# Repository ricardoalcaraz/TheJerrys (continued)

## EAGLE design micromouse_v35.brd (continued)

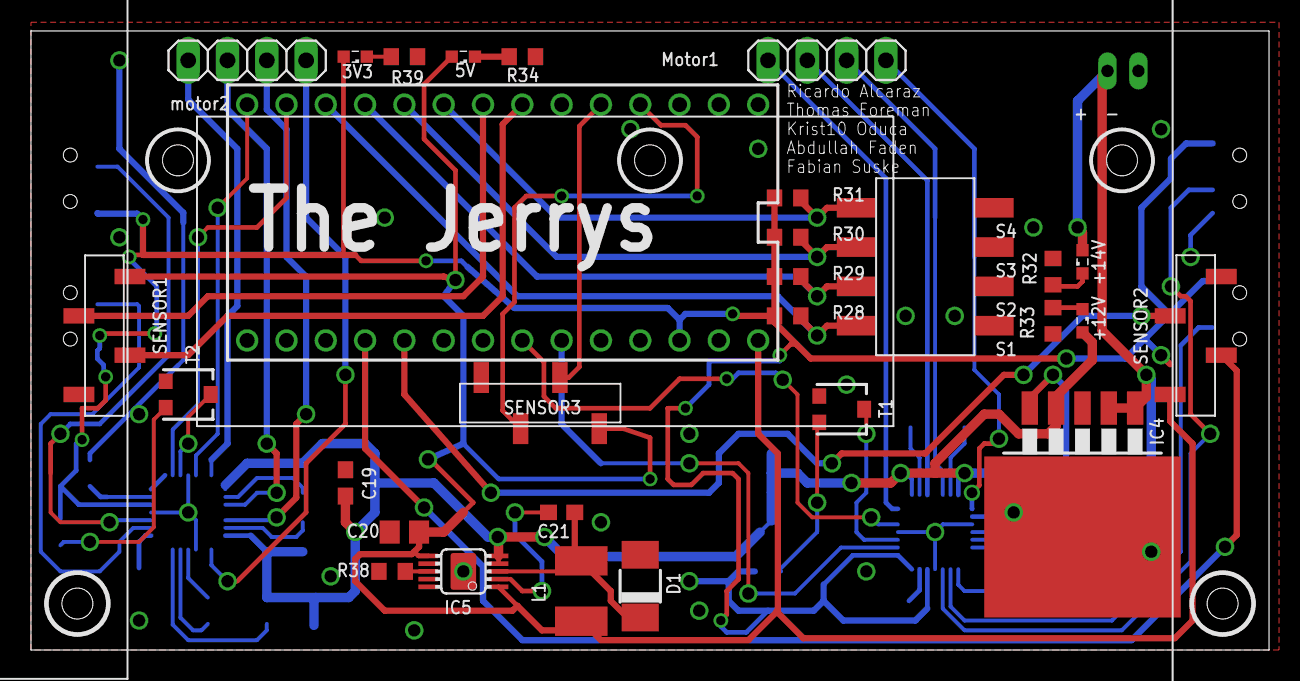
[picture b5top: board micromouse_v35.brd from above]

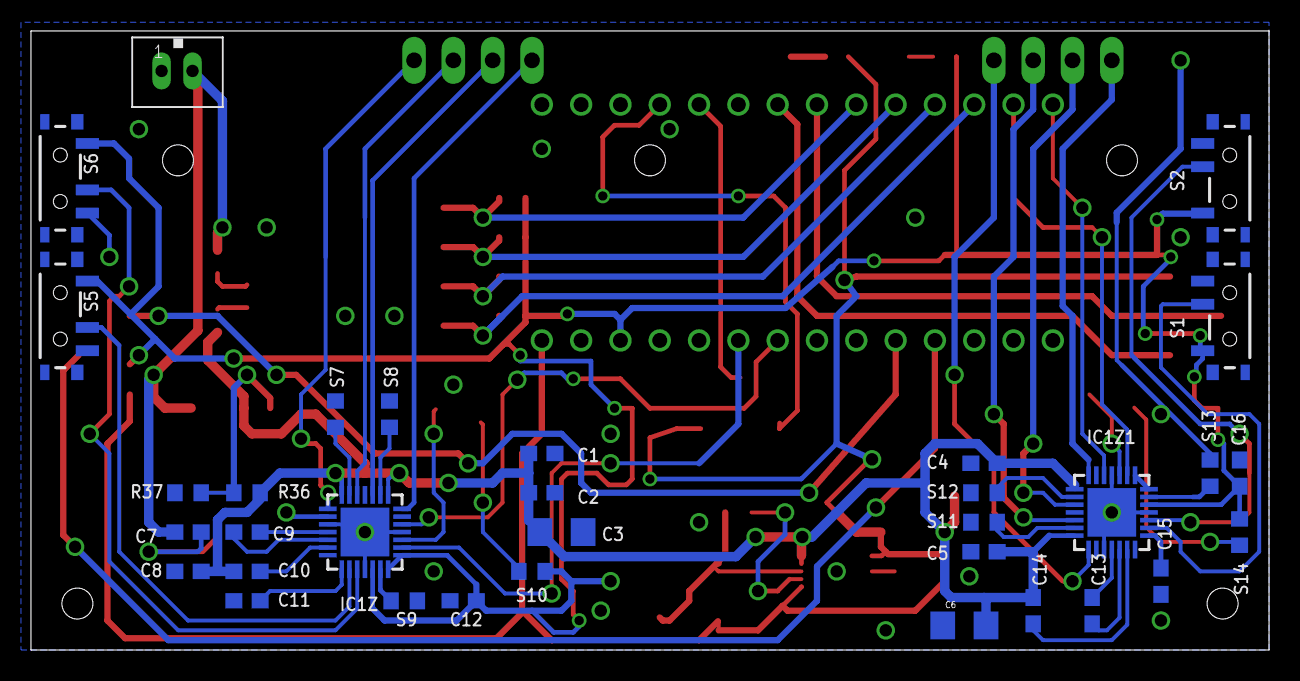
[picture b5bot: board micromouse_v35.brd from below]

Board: 2 copper layers, 80.0 x 40.0 mm, 62 parts (33 on the bottom side), 57 nets.

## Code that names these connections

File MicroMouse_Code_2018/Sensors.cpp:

#include "Sensors.h"

//Initializing an external functions so ISR can run properly
static void sensorISR();

//Pinout for the ultrasonic sensors
const uint8_t ECHO1 = 8;
const uint8_t ECHO2 = 2;
const uint8_t ECHO3 = 10;
const uint8_t TRIG1 = 9;
const uint8_t TRIG2 = 3;
const uint8_t TRIG3 = 11;
volatile double Sensors::runningAvgLeft[arraySize]={};
volatile double Sensors::runningAvgRight[arraySize]={};
volatile double Sensors::runningAvgMiddle[arraySize]={};

//Constructor
Sensors::Sensors( ) {
	//Set all the running average arrays to zero
	for( int i = 0; i < arraySize; i++ ) {
		runningAvgLeft[i] = 0;
		runningAvgRight[i] = 0;
		runningAvgMiddle[i] = 0;
	}
	timeout = 6000;
	interval = 10000;
}

//Initialize the pins for all the sensors
//Currently setup for ultrasonic sensors
void Sensors::init( uint32_t interval ) {
  	pinMode( ECHO2 ,INPUT );
  	pinMode( ECHO1 ,INPUT );
  	pinMode( ECHO3 ,INPUT );
  	pinMode( TRIG1 ,OUTPUT );
  	pinMode( TRIG2 ,OUTPUT );
  	pinMode( TRIG3 ,OUTPUT );
	this->interval = interval;
	sensorTimer.begin( sensorISR, this->interval );
	sensorTimer.priority( 50 );
}

void Sensors::setTimeout( uint32_t timeout ) {
	this->timeout = timeout;
}

//Return the averaged out right distance
double Sensors::getRightDistance( ) {
	uint16_t sum = 0;
	for( int i = 0; i < arraySize; i++ ) {
		sum += runningAvgRight[i];
	}
	double avg = sum/(double)arraySize+1;
	return avg;
}

//Return the averaged out left distance
double Sensors::getLeftDistance( ) {
	noInterrupts();
	double sum = 0;
	for( int i = 0; i < arraySize; i++ ) {
		sum += runningAvgLeft[i];
	}
	double avg = sum/(double)arraySize+1;
	interrupts();
	return avg;
}

//Return the averaged out middle distance
double Sensors::getMiddleDistance( ) {
	noInterrupts();
	double sum = 0;
	for( int i = 0; i < arraySize; i++ ) {
		sum += runningAvgMiddle[i];
	}
	interrupts();
	return sum/(double)arraySize+1;
}

//Update all the distances of the sensors
//and input them into the running average array
void Sensors::updateDistances() {
	static volatile uint8_t index = 0;
	static volatile uint8_t sensorCount = 0;
	switch( sensorCount ) {
		case 0:
			runningAvgLeft[index] = pingLeft();
			break;
		case 1:
			runningAvgRight[index] = pingRight();
			break;
		case 2:
			runningAvgMiddle[index] = pingMiddle();
			break;
	}
	index++;
	sensorCount++;
	if( index == arraySize ) index = 0;
	if( sensorCount == 3 ) sensorCount = 0;
}

//Return a single instance of the right sensor
volatile double Sensors::pingRight() {
      digitalWrite(TRIG2, LOW);
    delayMicroseconds(2);
    digitalWrite(TRIG2, HIGH);
    delayMicroseconds(10);
    digitalWrite(TRIG2, LOW);

    //Read the echo pin
    int duration = pulseIn(ECHO2, HIGH, timeout);

    //Calculate distance
    double distance = (double) duration*0.034/2;

    return distance;
}

//Return a single instance of the middle sensor
volatile double Sensors::pingLeft() {
    digitalWrite(TRIG3, LOW);
  	delayMicroseconds(2);
  	digitalWrite(TRIG3, HIGH);
  	delayMicroseconds(10);
  	digitalWrite(TRIG3, LOW);

  	//Read the echo pin
  	int duration = pulseIn(ECHO3, HIGH, timeout);

  	//Calculate distance
  	double distance = (double) duration*0.034/2;

  	return distance;
}

//Return a single instance of the middle sensor
volatile double Sensors::pingMiddle() {
  	digitalWrite(TRIG1, LOW);
  	delayMicroseconds(2);
  	digitalWrite(TRIG1, HIGH);
  	delayMicroseconds(10);
  	digitalWrite(TRIG1, LOW);

  	//Read the echo pin
  	int duration = pulseIn(ECHO1, HIGH, timeout);

  	//Calculate distance
  	double distance = (double) duration*0.034/2;

  	return distance;
}

Sensors sensorInterrupt;

//External interrupt function that points toward internal function, it's somewhat hacky but it works.
static void sensorISR() {
	sensorInterrupt.updateDistances();
}

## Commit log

2017-06-12 Added new schematic and board
2017-06-12 added motor control wiring
2017-06-12 Added sensor pins
2017-06-12 Added git ignore file
2017-06-12 Added small description of our project
2017-06-12 Added sensor pins to schematic
2017-06-12 Fixed Readme
2017-06-12 Finished Schematic Draft
2017-06-12 Fixed some inconsistencies
2017-07-20 Finalized Design
2017-07-20 Final final design
2017-07-20 Added 4pm to .gitignore
2017-07-20 Added description to readme
2017-07-20 Added ultrasonic sensor functions
2017-07-20 Added stepper motor + H bridge comm file that draws 0 current when inactive
2017-07-21 Fixed ability to read distances in serial monitor
    Added Serial.begin(9600) in order to initiate ability to read. Prior to this, sensor worked, but user could not read an output to confirm sensor's working ability. Additionally shifted delay after ch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
2017-07-21 Changed pulseMiddle() function to be able to output a distance
    pulseMiddle() used to just record and print distance. After changing its void return type to an int, it can now be treated as a variable and spit out a distance in cm. This will make it easier to eng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
2017-07-21 Replicated changes from pulseMiddle() to pulseRight() and pulseLeft()
    Lets user know when mouse can turn to make it easier to exxecute a turn. NOTE: if a single sensor gets very blocked as it nears an opening, measurements become really off and reach 3000cm. Since the 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
2017-07-21 Added file that combines sensor and motor
    Lets motor turn when sensor senses a gap. Still expends no current.
2017-07-21 Limit distance on sensors
    By setting the maximum time the sensor waits for a pulse, we can limit the maximum distance the pulse records. In this case, the sensor has been limited to 80cm.
2017-07-21 Updated combined sensor and motors to implement sensor range limitation
2017-07-22 Wrote code to implement a second motor
    Duplicated code and reassigned variable names. Cars will rotate on axis instead of pivoting. Therefore motor turning functions have both motors work at same time instead of having independent turning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
2017-07-22 Added turning functions given different pulses
2017-07-22 Added actual pin assignment for motors to the prototype board pin assignment
    Just comment out the prototype board/actual as necessary.
2017-07-25 Added file to start writing algorithm
    Will be able to solve using left hand rule and optimize for shortcuts
2017-07-25 renamed to more convenient variables
    Changed pins as well. in1Motor1 is now LMotor1
2017-07-25 Added switch functionality
    Using four switches in a case select scenario, we can 16 different possible outputs.
2017-07-25 Added new stepper library and functions
2017-07-26 consolidated useful functions in main file
2017-07-26 added missing code
2017-07-26 Wrote majority of algorithm pseudo-code
2017-07-26 Wrote additional code
    Got most of the logic for solving the maze and decision process written. Have not been able to test. Left FIXME comments for more experienced programmers to have a look at.
2017-07-26 Added comments describing various functions and fixed some setup code
2017-07-27 Edited code variables and included convenience delay
    Renamed motor pins to be motorLeft and motorRight instead of motor1 and motor 2. Additionally, there will be a delay after we flick the switch before the mouse starts working.
2017-07-27 Changed moveLeft and moveRight functions
    moveleft and move right no longer spin on its axis. It now pivots with one wheel stationary and the other incrementing steps. The functions are now named turnLeft() and turnRight(). Also removed the 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
2017-07-27 Combined all algorithm code into main micromouse.ino file.
2017-07-27 Ricardo, Khan, and Rosswell wrote code at same time via google docs
2017-07-27 Added a file to start simulating a maze and decision making
2017-07-27 Wrote a testbench for algorithm turning
    Program shows that it can optimize the path
2017-07-28 Ricardo and I group coded
    Wrote code to add letters and recall them to the directions as well as optimize.
2017-07-28 Fixed some compilation errors
2017-07-28 Fixed movment bugs
    corrected amount of steps bot shouyld take before it stop and decides again
2017-07-29 Consolidated bot functions into a new library
2017-07-29 Cleaned up some comments
2017-07-29 Begun adding ultrasonic sensor functions
    Only added basic pin assignments and setup
2017-07-29 added debug print statements
2017-07-29 Removed duplitcate
2017-07-29 Fixed pathing logic and started fine tuning movements
2017-07-29 Updated step counts
    steps cannot be 1 or else it will not move
2017-07-29 Changed middleDistance threshold to increase clearance when turning around
2017-07-29 Added path correcting to library
2017-07-29 Added path correction and minor micromouse.ino files
2017-07-29 Deleted jerry and stepper libraries as they should be in same folder level as main micromouse.ino
2017-07-29 No idea
2017-07-29 Revert "Deleted jerry and stepper libraries as they should be in same folder level as main micromouse.ino"
    This reverts commit 5623b765bdf1a9f3894e21da4fe20d62e673050c.
2017-08-01 Added last seconds corrections
2017-08-16 Added distance averaging
    Now has a small buffer and records 3 distances. The distance that is given is the median of 3 recordings to reduce the chance of an erroneous reading
2017-08-24 Fixed various compilation errors
2017-08-25 Fixed compilation errors
2017-08-25 Made comments to lgoic
2017-08-27 Added some commentary to the logic behind maze solving
2017-09-05 Added descriptions to various functions
2017-11-02 Testbenched method to check if mouse found goal
2017-11-02 Wrote code to test if mouse found goal
    Wrote isGoal() to check if three right turns were made in a row while under a set number of steps. Since I learned about pointers, I wrote clearCounter() to clear the steps made unless a right turn w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
2017-11-18 Changed algorithm tests to use address passing
2018-01-25 Polished board and added names
2018-03-11 Added makeTurn() function
2018-03-11 Added another simulation based on an actual maze
2018-03-11 Deleted unnecessary files
2018-03-11 Cleaned up some files
2018-03-11 Transfered test algorithm code to micromouse.ino
2018-03-12 Added file to test intersections
2018-03-12 Started 2018 board revision for micromouse
2018-03-12 Added power switch to schematic
2018-03-20 Added power circuit
2018-03-21 Changed SS31FL diode to CMS06 for better heat dissipation
2018-03-22 Rough draft for 5V power circuit layout
2018-03-25 Created 12V layout, removed thermals on 5V layout
2018-03-28 Completed Board layout, passed DRC, removed 2 status LEDs, increased C6 C7
2018-04-03 Fixed some silkscreen labels
2018-04-04 Made mounting holes a bit smaller
2018-05-18 Seperated out code into 2017 and 2018
2018-05-18 Added move forward functions
2018-05-22 Added some more functions to the motors class
2018-05-22 Tuned the turn left and turn right functions
2018-05-22 Tuned move forward some more
2018-05-22 Added some changes to motor functions
2018-05-22 Added misc notes section
2018-05-25 Fixed all motor turning functions
2018-05-25 Added a turn around feature, perfected motor functions and added code documentation
2018-05-25 Fixed interference issues with sensors
2018-05-25 Separated test functions and cleared while loop to test functions
2018-05-25 Added the move backward function
2018-05-25 Wrote and tested code for getIntersection()
2018-05-25 Wrote and tested isIntersection
2018-05-25 Added some movement functions
2018-05-26 Added more motor movement functions
2018-05-26 Refactored turning functions
2018-06-06 Included simulation tested isGoal and optimize functions
2018-06-06 Added higher level abstraction for turning
2018-06-06 readded solvemaze and solveoptimized
2018-06-06 Added motor functions
2018-06-08 Reverified getIntersection() on good hardware, changed wall thresholds to accomodate getDistances instead of getPings
2018-06-08 Major motor rework: changed ricardo's code
2018-06-08 Added tank turns + some comments
2018-06-09 Created new Motor headers
2018-06-09 Wrote imperfect turning sequences
2018-06-09 Verified isIntersection(), started P(id) controll system
2018-06-10 PID controller for lanekeeping
2018-06-10 Changed motor millisecond delay to microsecond delay for PID
2018-06-10 Tuned PID and included UTURN
2018-06-13 Worked on basic turn functionality
2018-06-13 Wrote a debounced version of makeTurn()
2018-06-14 Tuned PID, modified main loop to make robot solve maze by crashing into walls
2018-06-14 callibrated auto forward pid to go to the middle of the cell for intersections
2018-06-17 New changes
2018-06-17 Reverted sensor and updated pid system
2018-06-17 Worked on PID
2018-06-17 Tuned pid
2018-06-19 Changed pid values to consistently work in hallways and uturn
    Tested hallway/uturn to work for 2+mins
2018-06-26 Cleaned up main code
2018-06-27 Fixed autoForward centering callibration. Had fairly consistent straights and cornering prior to hardware blowing up
2018-07-19 2019 update
2018-07-19 2019 update second commit
2018-07-19 cleaned up dir names
2018-07-19 Readme
2018-07-19 deleted redundant files
2018-07-19 calculating distances
2018-07-19 calculated distances displayed in maze
2018-07-19 Added initWalls() and made printMaze() read from cell[][]
2018-07-20 Added floodfill function definitions + descriptions
2018-07-20 finished wall updating subroutines
2018-07-20 Finished all but updateDistances() floodfill functions
2018-07-21 Wrote updateDistances()
2018-07-21 updateDistances() Working
2018-07-21 improved style
2018-07-22 Placed functions in headers
2019-03-02 Altium Schematic
